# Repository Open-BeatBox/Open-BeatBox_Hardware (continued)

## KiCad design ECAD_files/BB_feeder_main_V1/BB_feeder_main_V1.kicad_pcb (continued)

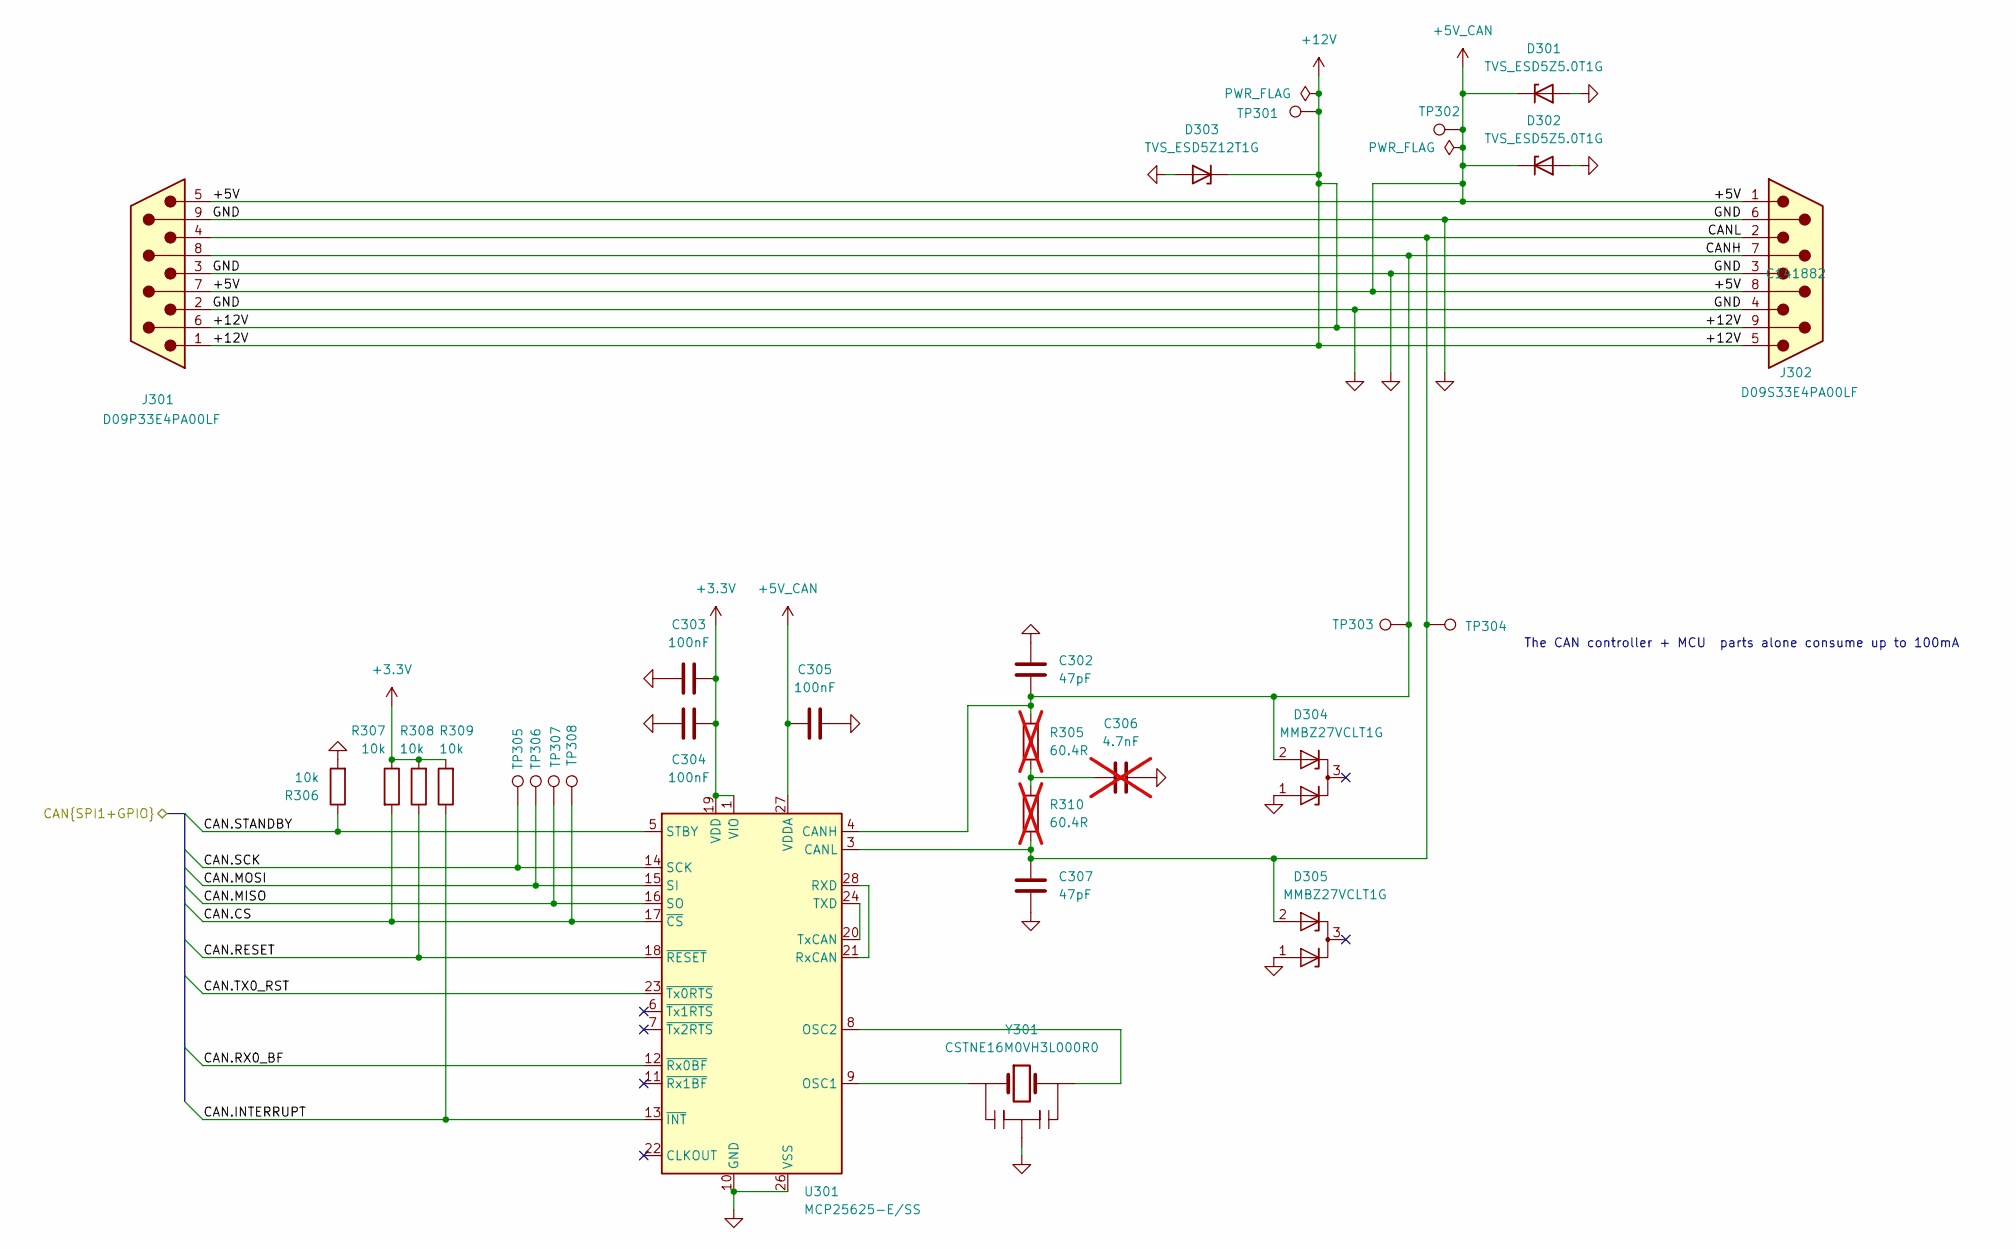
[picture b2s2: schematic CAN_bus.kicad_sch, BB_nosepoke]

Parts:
C302, C307: 47pF; C_0603_1608Metric
C303, C304, C305: 100nF; C_0603_1608Metric
C306: 4.7nF; C_0603_1608Metric; not fitted
D301, D302: TVS_ESD5Z5.0T1G; D_SOD-523; MPN ESD5Z5.0T1G; JLC Part C343989
D303: TVS_ESD5Z12T1G; D_SOD-523; MPN ESD5Z12T1G
D304, D305: MMBZ27VCLT1G; SOT-23; MPN MMBZ27VCLT1G; JLC Part C128609
J301: Conn-DB9_D09P33E4PA00LF; Conn_DB9_D09P33E4PA00LF; MPN D09P33E4PA00LF; JLC Part C19077344
J302: Conn-DB9_D09S33E4PA00LF; Conn_DB9_D09S33E4PA00LF; MPN D09S33E4PA00LF; JLC Part C141882
R305, R310: 60.4R; R_0603_1608Metric; not fitted
R306, R307, R308, R309: 10k; R_0603_1608Metric
TP301, TP302: TestPoint; TestPoint_THTPad_D2.0mm_Drill1.0mm
TP303, TP304, TP305, TP306, TP307, TP308: TestPoint; TestPoint_Pad_D1.0mm
U301: MCP25625-E/SS; SSOP-28_5.3x10.2mm_P0.65mm; MPN MCP25625-E/SS; JLC Part C184944
Y301: CSTNE16M0VH3L000R0; Resonator_SMD_Murata_CSTxExxV-3Pin_3.0x1.1mm; MPN CSTNE16M0VH3L000R0; JLC Part C1870467

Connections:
+3.3V: C303.2, C304.2, R307.1, R308.2, R309.2, U301.1 (VIO), U301.19 (VDD); also elsewhere on the board
+5V_CAN: C305.1, D301.1 (K), D302.1 (K), J301.5, J301.7, J302.1, J302.8, TP302.1 (1_1), U301.27 (VDDA); also elsewhere on the board
+12V: D303.1 (K), J301.1, J301.6, J302.5, J302.9, TP301.1 (1_1); also elsewhere on the board
/CAN bus/CAN.CS: R307.2, TP308.1 (1_1), U301.17 (~CS); also elsewhere on the board
/CAN bus/CAN.INTERRUPT: R309.1, U301.13 (~INT); also elsewhere on the board
/CAN bus/CAN.MISO: TP307.1 (1_1), U301.16 (SO); also elsewhere on the board
/CAN bus/CAN.MOSI: TP306.1 (1_1), U301.15 (SI); also elsewhere on the board
/CAN bus/CAN.RESET: R308.1, U301.18 (~RESET); also elsewhere on the board
/CAN bus/CAN.RX0_BF: U301.12 (~Rx0BF); also elsewhere on the board
/CAN bus/CAN.SCK: TP305.1 (1_1), U301.14 (SCK); also elsewhere on the board
/CAN bus/CAN.STANDBY: R306.1, U301.5 (STBY); also elsewhere on the board
/CAN bus/CAN.TX0_RST: U301.23 (~Tx0RTS); also elsewhere on the board
/CAN bus/CANH: C302.2, D304.2 (K), J301.8, J302.7, R305.2, TP303.1 (1_1), U301.4 (CANH)
/CAN bus/CANL: C307.1, D305.2 (K), J301.4, J302.2, R310.1, TP304.1 (1_1), U301.3 (CANL)
GND: C302.1, C303.1, C304.1, C305.2, C306.2, C307.2, D301.2 (A), D302.2 (A), D303.2 (A), D304.1 (K), D305.1 (K), J301.2, J301.3, J301.9, J302.3, J302.4, J302.6, R306.2, U301.10 (GND), U301.26 (VSS), Y301.2 (GND); also elsewhere on the board
unnamed: C306.1, R305.1, R310.2
unnamed: U301.9 (OSC1), Y301.1 (Input)
unnamed: U301.8 (OSC2), Y301.3 (Output)
unnamed: U301.21 (RxCAN), U301.28 (RXD)
unnamed: U301.20 (TxCAN), U301.24 (TXD)

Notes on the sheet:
The CAN controller + MCU parts alone consume up to 100mA

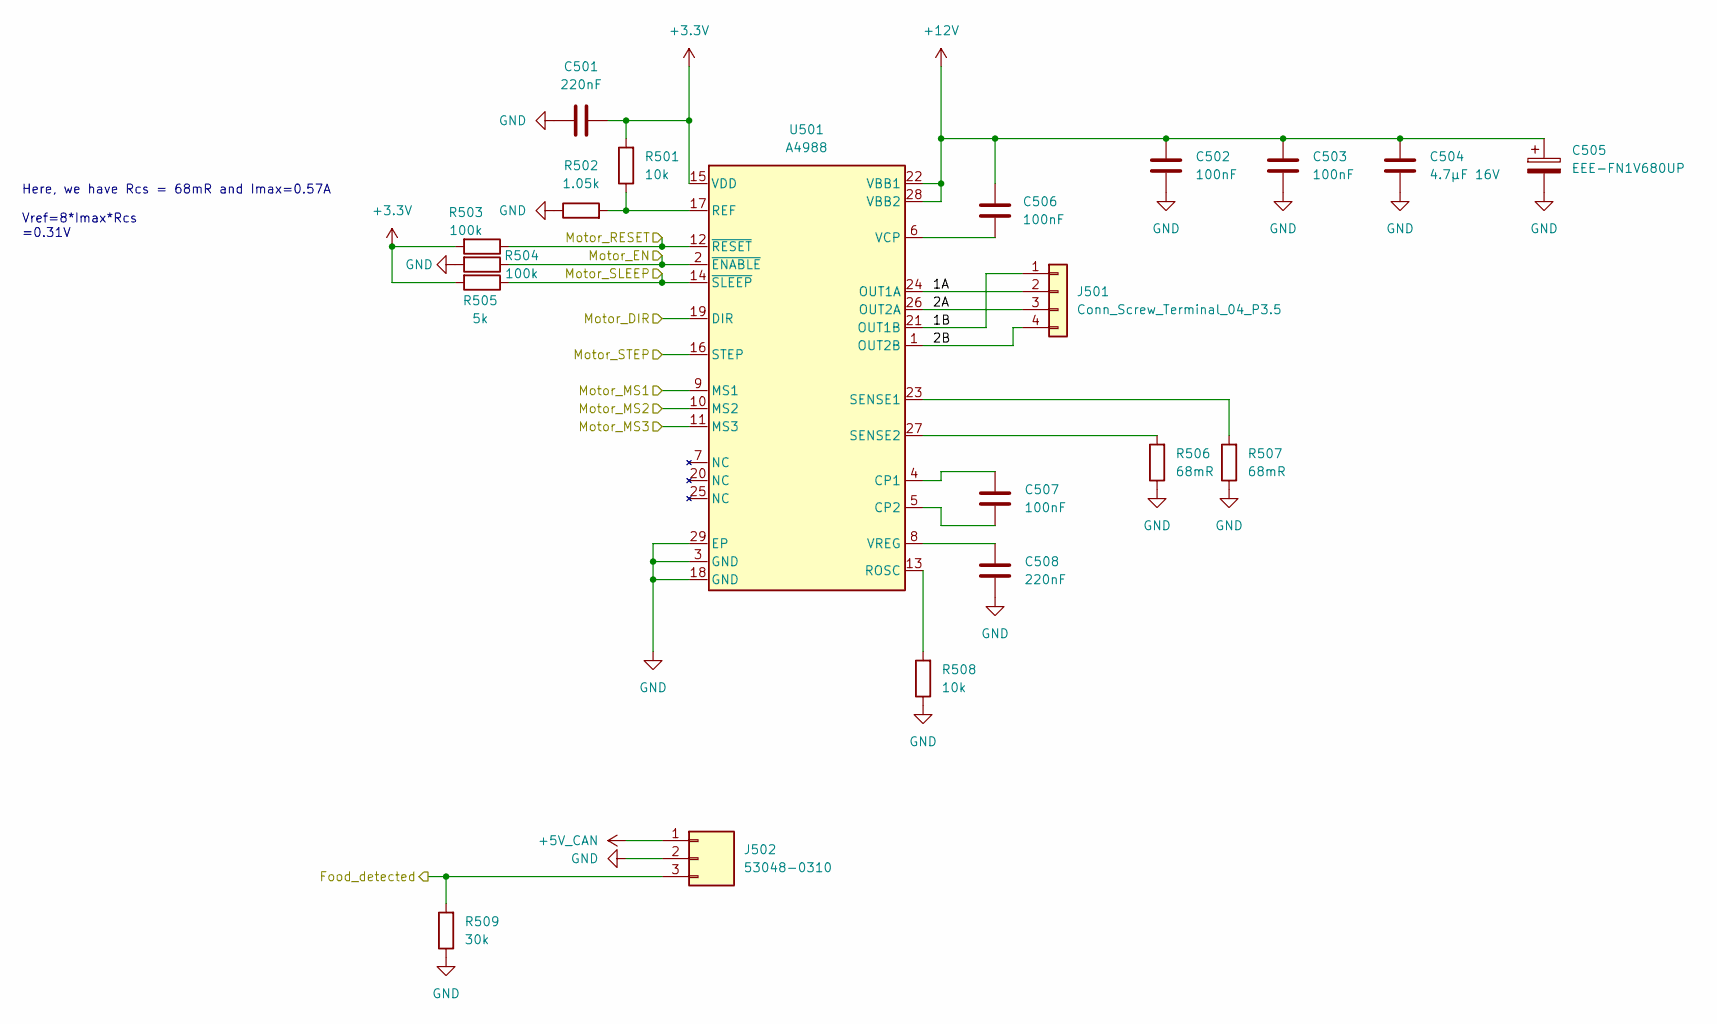
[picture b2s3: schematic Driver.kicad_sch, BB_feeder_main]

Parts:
C501, C508: 220nF; C_0603_1608Metric
C502, C503, C506, C507: 100nF; C_0603_1608Metric
C504: 4.7µF 16V; C_1206_3216Metric
C505: EEE-FN1V680UP; MPN EEE-FN1V680UP
J501: Conn_Screw_Terminal_04_P3.5; TerminalBlock_Phoenix_PT-1,5-4-3.5-H_1x04_P3.50mm_Horizontal; MPN 20020327-C041B01LF; JLC Part C2757925
J502: Conn_Picoblade_Molex_53048-0310; Conn_Molex_PicoBlade_53048-0310_1x03_P1.25mm_Horizontal; MPN 53048-0310; JLC Part C505275
R501, R508: 10k; R_0603_1608Metric
R502: 1.05k; R_0603_1608Metric
R503, R504: 100k; R_0603_1608Metric
R505: 5k; R_0603_1608Metric
R506, R507: 68mR; R_0603_1608Metric
R509: 30k; R_0603_1608Metric
U501: A4988; QFN-28-1EP_5x5mm_P0.5mm_EP3.1x3.1mm; MPN A4988SETTR-T

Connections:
+3.3V: C501.1, R501.2, R503.2, R505.2, U501.15 (VDD); also elsewhere on the board
+5V_CAN: J502.1; also elsewhere on the board
+12V: C502.1, C503.1, C504.1, C505.2, C506.2, U501.22 (VBB1), U501.28 (VBB2); also elsewhere on the board
/MCU/Food_detected: J502.3, R509.2; also elsewhere on the board
/MCU/Motor_DIR: U501.19 (DIR); also elsewhere on the board
/MCU/Motor_EN: R504.1, U501.2 (~ENABLE); also elsewhere on the board
/MCU/Motor_MS1: U501.9 (MS1); also elsewhere on the board
/MCU/Motor_MS2: U501.10 (MS2); also elsewhere on the board
/MCU/Motor_MS3: U501.11 (MS3); also elsewhere on the board
/MCU/Motor_RESET: R503.1, U501.12 (~RESET); also elsewhere on the board
/MCU/Motor_SLEEP: R505.1, U501.14 (~SLEEP); also elsewhere on the board
/MCU/Motor_STEP: U501.16 (STEP); also elsewhere on the board
/Motor driver/1A: J501.2, U501.24 (OUT1A)
/Motor driver/1B: J501.1, U501.21 (OUT1B)
/Motor driver/2A: J501.3, U501.26 (OUT2A)
/Motor driver/2B: J501.4, U501.1 (OUT2B)
GND: C501.2, C502.2, C503.2, C504.2, C505.1, C508.2, J502.2, R502.1, R504.2, R506.1, R507.1, R508.1, R509.1, U501.3 (GND), U501.18 (GND), U501.29 (EP); also elsewhere on the board
unnamed: C507.1, U501.4 (CP1)
unnamed: C507.2, U501.5 (CP2)
unnamed: R501.1, R502.2, U501.17 (REF)
unnamed: R508.2, U501.13 (ROSC)
unnamed: R507.2, U501.23 (SENSE1)
unnamed: R506.2, U501.27 (SENSE2)
unnamed: C506.1, U501.6 (VCP)
unnamed: C508.1, U501.8 (VREG)

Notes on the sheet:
Here, we have Rcs = 68mR and Imax=0.57A Vref=8*Imax*Rcs =0.31V

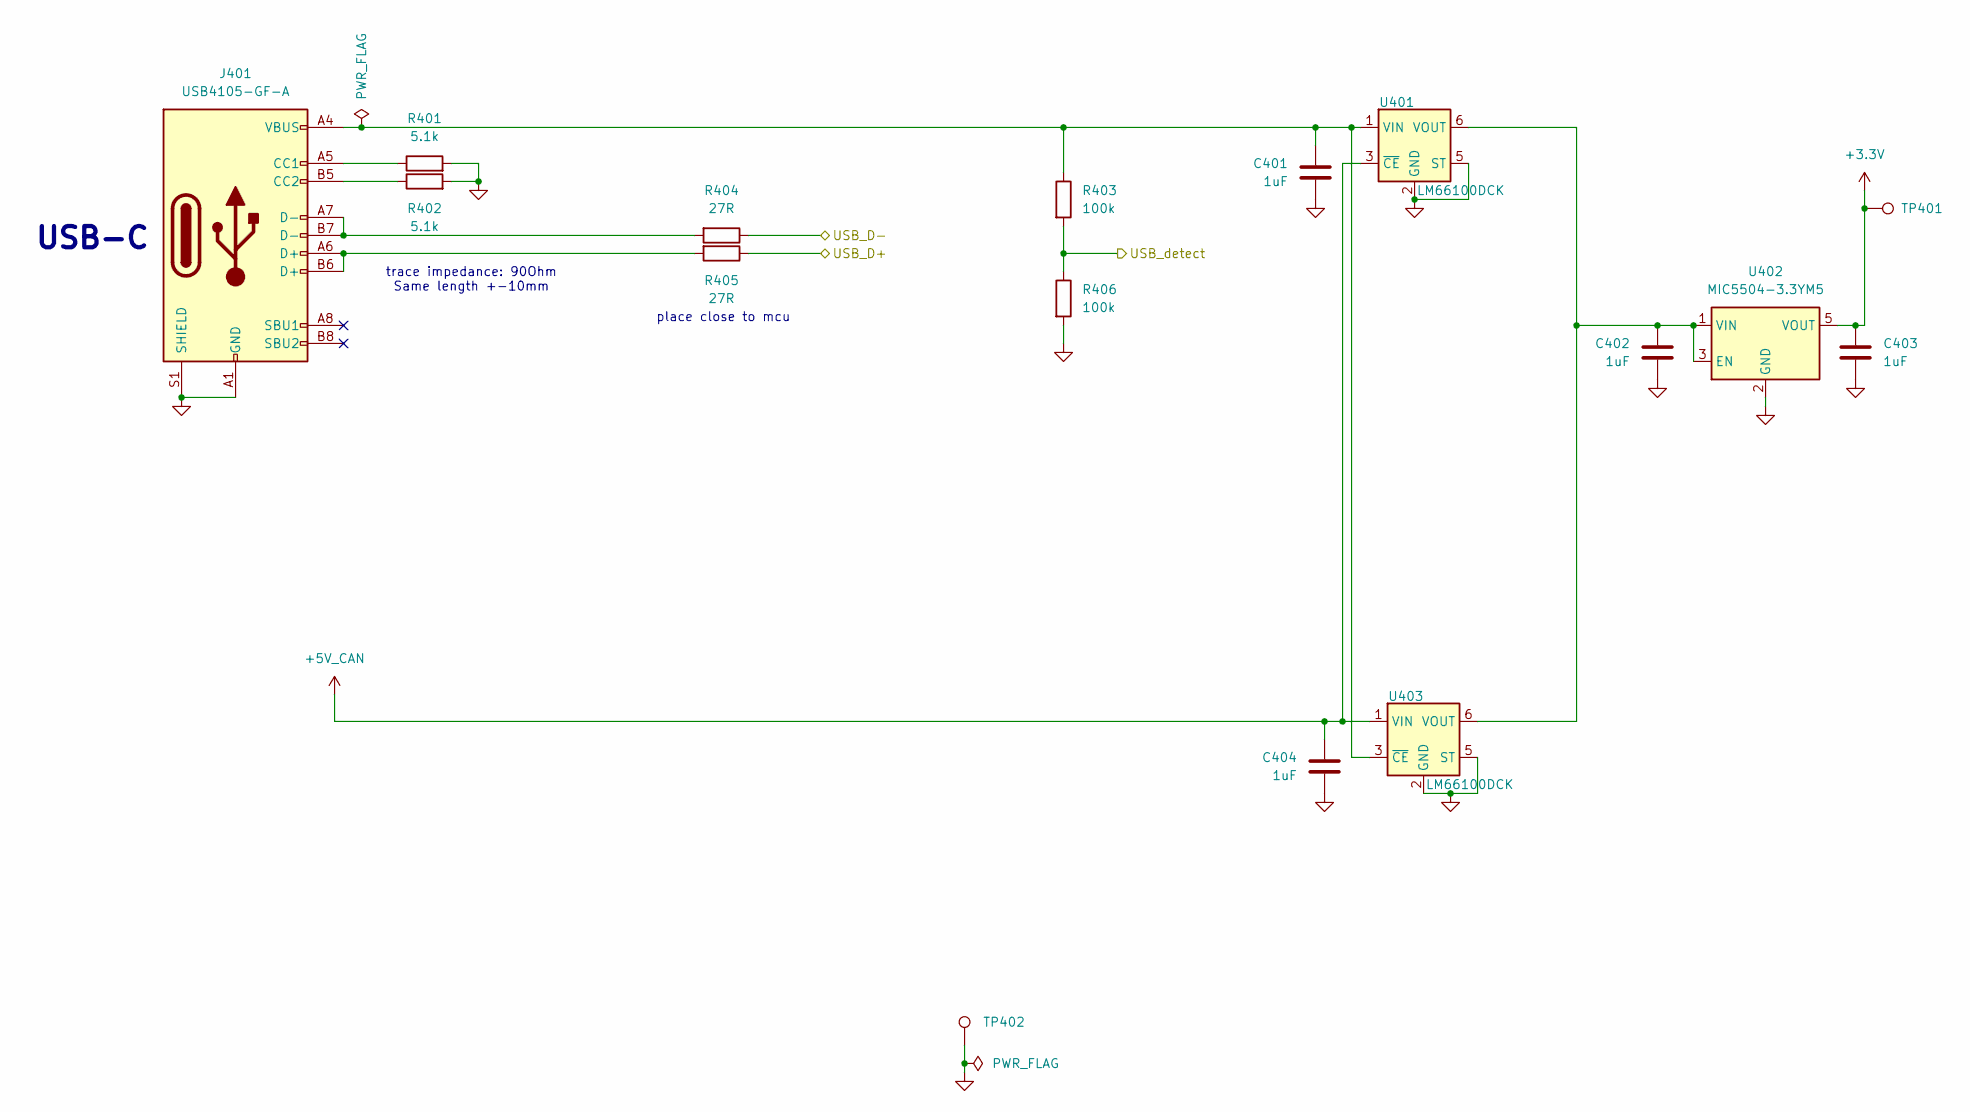
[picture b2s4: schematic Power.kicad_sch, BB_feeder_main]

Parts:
C401, C402, C403, C404: 1uF; C_0603_1608Metric
J401: Conn_USB-C_USB4105-GF-A; Conn_USB_C_Receptacle_GCT_USB4105-xx-A_16P_TopMnt_Horizontal; MPN USB4105-GF-A; JLC Part C393939
R401, R402: 5.1k; R_0603_1608Metric
R403, R406: 100k; R_0603_1608Metric
R404, R405: 27R; R_0603_1608Metric
TP401, TP402: TestPoint; TestPoint_THTPad_D2.0mm_Drill1.0mm
U401, U403: LM66100DCK; SOT-363_SC-70-6; MPN LM66100DCKR; JLC Part C2869734
U402: MIC5504-3.3YM5; SOT-23-5; MPN MIC5504-3.3YM5; JLC Part C88419

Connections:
+3.3V: C403.1, TP401.1 (1_1), U402.5 (VOUT); also elsewhere on the board
+5V_CAN: C404.2, U401.3 (~CE), U403.1 (VIN); also elsewhere on the board
/MCU/USB_D+: R405.1; also elsewhere on the board
/MCU/USB_D-: R404.1; also elsewhere on the board
/MCU/USB_detect: R403.2, R406.1; also elsewhere on the board
GND: C401.1, C402.2, C403.2, C404.1, J401.A1 (GND), J401.A12 (GND), J401.B1 (GND), J401.B12 (GND), J401.S1 (SHIELD), R401.2, R402.2, R406.2, TP402.1 (1_1), U401.2 (GND), U401.5 (ST), U402.2 (GND), U403.2 (GND), U403.5 (ST); also elsewhere on the board
unnamed: J401.A5 (CC1), R401.1
unnamed: J401.B5 (CC2), R402.1
unnamed: J401.A6 (D+), J401.B6 (D+), R405.2
unnamed: J401.A7 (D-), J401.B7 (D-), R404.2
unnamed: C401.2, J401.A4 (VBUS), J401.A9 (VBUS), J401.B4 (VBUS), J401.B9 (VBUS), R403.1, U401.1 (VIN), U403.3 (~CE)
unnamed: C402.1, U401.6 (VOUT), U402.1 (VIN), U402.3 (EN), U403.6 (VOUT)

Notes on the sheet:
place close to mcu
trace impedance: 90Ohm Same length +-10mm
USB-C

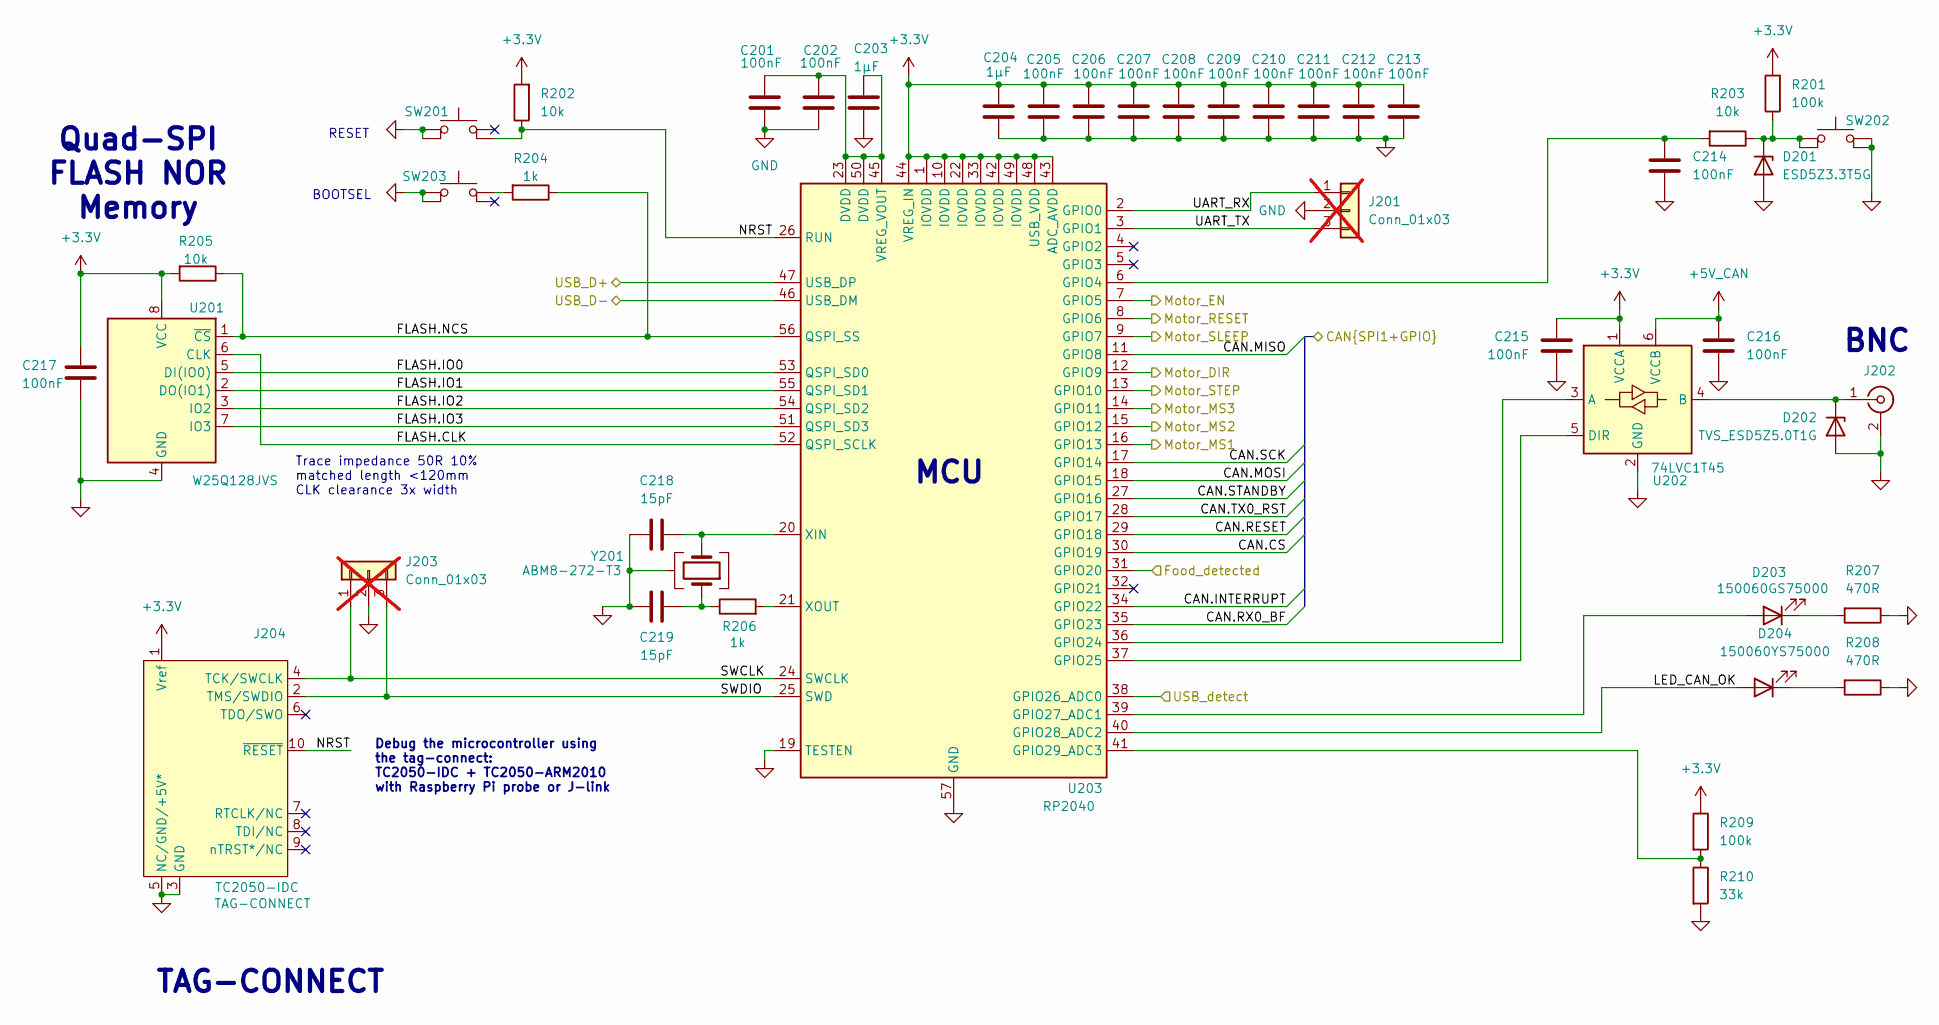
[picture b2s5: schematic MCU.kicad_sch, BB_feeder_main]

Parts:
C201, C202, C205, C206, C207, C208, C209, C210, C211, C212, C213, C214, C215, C216, C217: 100nF; C_0603_1608Metric
C203, C204: 1µF; C_0603_1608Metric
C218, C219: 15pF; C_0603_1608Metric
D201: TVS_ESD5Z3.3T5G; D_SOD-523; MPN ESD5Z3.3T5G; JLC Part C22440024
D202: TVS_ESD5Z5.0T1G; D_SOD-523; MPN ESD5Z5.0T1G; JLC Part C343989
D203: LED_150060GS75000; LED_0603_1608Metric; MPN 150060GS75000; JLC Part C5252984
D204: LED_150060YS75000; LED_0603_1608Metric; MPN 150060YS75000; JLC Part C6784997
J201, J203: Conn_01x03; PinHeader_1x03_P2.54mm_Vertical; not fitted
J202: Conn_BNC_KH-BNC50-3511; KH-BNC50-3511; MPN KH-BNC50-3511; JLC Part C2837587
J204: Conn_TagConnect_TC2050-IDC; Tag-Connect_TC2050-IDC-FP_2x05_P1.27mm_Vertical; MPN TC2050-IDC
R201, R209: 100k; R_0603_1608Metric
R202, R203, R205: 10k; R_0603_1608Metric
R204, R206: 1k; R_0603_1608Metric
R207, R208: 470R; R_0603_1608Metric
R210: 33k; R_0603_1608Metric
SW201, SW202, SW203: SW_TL3305AF160QG; SW_Push_TL3305; MPN TL3305AF160QG; JLC Part C18078070
U201: W25Q128JVS; SOIC-8_W25Q128JV; MPN W25Q128JVS; JLC Part C97521
U202: 74LVC1T45; SOT-363_SC-70-6; MPN 74LVC1T45DW-7; JLC Part C168855
U203: RP2040; QFN-56-1EP_7x7mm_P0.4mm_EP3.2x3.2mm; MPN RP2040; JLC Part C2040
Y201: Crystal_ABM8-272-T3; Crystal_SMD_Abracon_ABM8; MPN ABM8-272-T3; JLC Part C20625731

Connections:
+3.3V: C204.1, C205.1, C206.1, C207.1, C208.1, C209.1, C210.1, C211.1, C212.1, C213.1, C215.2, C217.2, J204.1 (Vref), R201.2, R202.2, R205.2, R209.1, U201.8 (VCC), U202.1 (VCCA), U203.1 (IOVDD), U203.10 (IOVDD), U203.22 (IOVDD), U203.33 (IOVDD), U203.42 (IOVDD), U203.43 (ADC_AVDD), U203.44 (VREG_IN), U203.48 (USB_VDD), U203.49 (IOVDD); also elsewhere on the board
+5V_CAN: C216.2, U202.6 (VCCB); also elsewhere on the board
/CAN bus/CAN.CS: U203.30 (GPIO19); also elsewhere on the board
/CAN bus/CAN.INTERRUPT: U203.34 (GPIO22); also elsewhere on the board
/CAN bus/CAN.MISO: U203.11 (GPIO8); also elsewhere on the board
/CAN bus/CAN.MOSI: U203.18 (GPIO15); also elsewhere on the board
/CAN bus/CAN.RESET: U203.29 (GPIO18); also elsewhere on the board
/CAN bus/CAN.RX0_BF: U203.35 (GPIO23); also elsewhere on the board
/CAN bus/CAN.SCK: U203.17 (GPIO14); also elsewhere on the board
/CAN bus/CAN.STANDBY: U203.27 (GPIO16); also elsewhere on the board
/CAN bus/CAN.TX0_RST: U203.28 (GPIO17); also elsewhere on the board
/MCU/FLASH.CLK: U201.6 (CLK), U203.52 (QSPI_SCLK)
/MCU/FLASH.IO0: U201.5 (DI(IO0)), U203.53 (QSPI_SD0)
/MCU/FLASH.IO1: U201.2 (DO(IO1)), U203.55 (QSPI_SD1)
/MCU/FLASH.IO2: U201.3 (IO2), U203.54 (QSPI_SD2)
/MCU/FLASH.IO3: U201.7 (IO3), U203.51 (QSPI_SD3)
/MCU/FLASH.NCS: R204.1, R205.1, U201.1 (~CS), U203.56 (QSPI_SS)
/MCU/Food_detected: U203.31 (GPIO20); also elsewhere on the board
/MCU/LED_CAN_OK: D204.2 (A), U203.40 (GPIO28_ADC2)
/MCU/Motor_DIR: U203.12 (GPIO9); also elsewhere on the board
/MCU/Motor_EN: U203.7 (GPIO5); also elsewhere on the board
/MCU/Motor_MS1: U203.16 (GPIO13); also elsewhere on the board
/MCU/Motor_MS2: U203.15 (GPIO12); also elsewhere on the board
/MCU/Motor_MS3: U203.14 (GPIO11); also elsewhere on the board
/MCU/Motor_RESET: U203.8 (GPIO6); also elsewhere on the board
/MCU/Motor_SLEEP: U203.9 (GPIO7); also elsewhere on the board
/MCU/Motor_STEP: U203.13 (GPIO10); also elsewhere on the board
/MCU/NRST: J204.10 (~RESET), R202.1, SW201.2, U203.26 (RUN)
/MCU/SWCLK: J203.1, J204.4 (TCK/SWCLK), U203.24 (SWCLK)
/MCU/SWDIO: J203.3, J204.2 (TMS/SWDIO), U203.25 (SWD)
/MCU/UART_RX: J201.1, U203.2 (GPIO0)
/MCU/UART_TX: J201.3, U203.3 (GPIO1)
/MCU/USB_D+: U203.47 (USB_DP); also elsewhere on the board
/MCU/USB_D-: U203.46 (USB_DM); also elsewhere on the board
/MCU/USB_detect: U203.38 (GPIO26_ADC0); also elsewhere on the board
GND: C201.1, C202.2, C203.1, C204.2, C205.2, C206.2, C207.2, C208.2, C209.2, C210.2, C211.2, C212.2, C213.2, C214.2, C215.1, C216.1, C217.1, C218.1, C219.1, D201.2 (A), D202.2 (A), J201.2, J202.2 (Ext), J203.2, J204.3 (GND), J204.5 (NC/GND/+5V*), R207.1, R208.1, R210.2, SW201.3, SW201.4, SW202.3, SW202.4, SW203.1, SW203.2, U201.4 (GND), U202.2 (GND), U203.19 (TESTEN), U203.57 (GND), Y201.2, Y201.4; also elsewhere on the board
unnamed: C219.2, R206.1, Y201.1
unnamed: D201.1 (K), R201.1, R203.1, SW202.1, SW202.2
unnamed: D202.1 (K), J202.1 (In), U202.4 (B)
unnamed: D203.2 (A), U203.39 (GPIO27_ADC1)
unnamed: D203.1 (K), R207.2
unnamed: D204.1 (K), R208.2
unnamed: R204.2, SW203.3
unnamed: U202.3 (A), U203.36 (GPIO24)
unnamed: U202.5 (DIR), U203.37 (GPIO25)
unnamed: C214.1, R203.2, U203.6 (GPIO4)
unnamed: R209.2, R210.1, U203.41 (GPIO29_ADC3)
unnamed: C201.2, C202.1, C203.2, U203.23 (DVDD), U203.45 (VREG_VOUT), U203.50 (DVDD)
unnamed: C218.2, U203.20 (XIN), Y201.3
unnamed: R206.2, U203.21 (XOUT)

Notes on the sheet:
Trace impedance 50R 10% matched length <120mm CLK clearance 3x width
RESET
Quad-SPI FLASH NOR Memory
Debug the microcontroller using the tag-connect: TC2050-IDC + TC2050-ARM2010 with Raspberry Pi probe or J-link
TAG-CONNECT
MCU
BNC
BOOTSEL

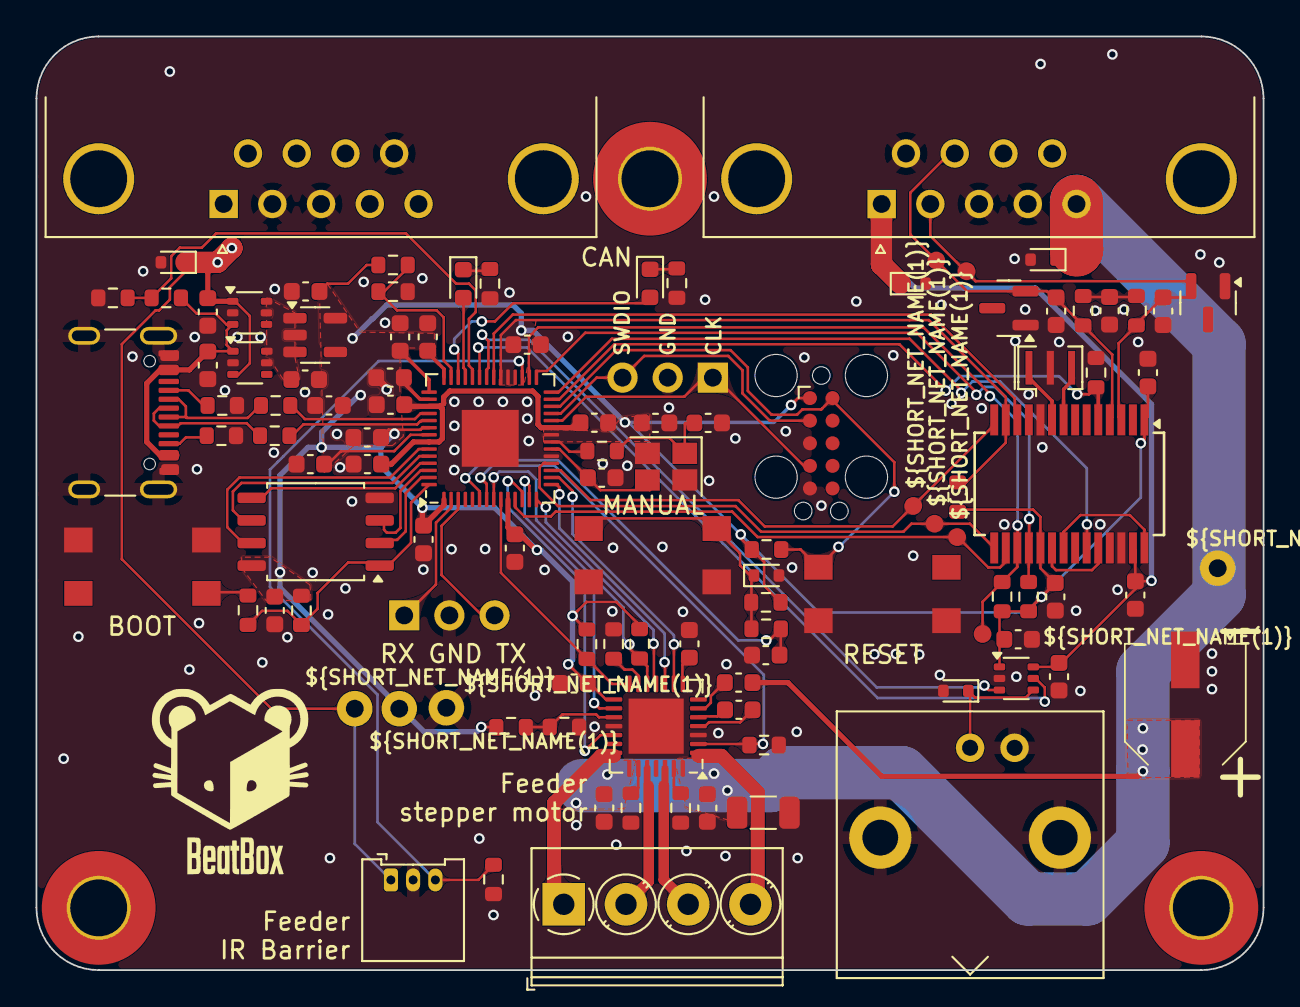
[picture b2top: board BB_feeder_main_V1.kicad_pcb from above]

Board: 4 copper layers, 69.0 x 52.5 mm, 112 parts (0 on the bottom side), 76 nets.

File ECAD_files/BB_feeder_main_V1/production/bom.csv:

Designator,Footprint,Quantity,Value,LCSC Part #
"C201, C202, C205, C206, C207, C208, C209, C210, C211, C212, C213, C214, C215, C216, C217, C303, C304, C305, C502, C503, C506, C507",0603,22,100nF,
"C203, C204",0603,2,1µF,
"C218, C219",0603,2,15pF,
"C302, C307",0603,2,47pF,
"C401, C402, C403, C404",0603,4,1uF,
"C501, C508",0603,2,220nF,
C504,1206,1,4.7µF 16V,
C505,EEE-FN1V680UP,1,EEE-FN1V680UP,EEE-FN1V680UP
D201,D_SOD-523,1,TVS_ESD5Z3.3T5G,ESD5Z3.3T5G
"D202, D301, D302",D_SOD-523,3,TVS_ESD5Z5.0T1G,ESD5Z5.0T1G
D203,0603,1,LED_150060GS75000,150060GS75000
D204,0603,1,LED_150060YS75000,150060YS75000
D303,D_SOD-523,1,TVS_ESD5Z12T1G,ESD5Z12T1G
"D304, D305",SOT-23,2,MMBZ27VCLT1G,MMBZ27VCLT1G
J202,KH-BNC50-3511,1,Conn_BNC_KH-BNC50-3511,KH-BNC50-3511
J301,Conn_DB9_D09P33E4PA00LF,1,Conn-DB9_D09P33E4PA00LF,D09P33E4PA00LF
J302,Conn_DB9_D09S33E4PA00LF,1,Conn-DB9_D09S33E4PA00LF,D09S33E4PA00LF
J401,Conn_USB_C_Receptacle_GCT_USB4105-xx-A_16P_TopMnt_Horizontal,1,Conn_USB-C_USB4105-GF-A,USB4105-GF-A
J501,"TerminalBlock_Phoenix_PT-1,5-4-3.5-H_1x04_P3.50mm_Horizontal",1,Conn_Screw_Terminal_04_P3.5,20020327-C041B01LF
J502,Conn_Molex_PicoBlade_53048-0310_1x03_P1.25mm_Horizontal,1,Conn_Picoblade_Molex_53048-0310,53048-0310
"R201, R209, R403, R406, R503, R504",0603,6,100k,
"R202, R203, R205, R306, R307, R308, R309, R501, R508",0603,9,10k,
"R204, R206",0603,2,1k,
"R207, R208",0603,2,470R,
R210,0603,1,33k,
"R401, R402",0603,2,5.1k,
"R404, R405",0603,2,27R,
R502,0603,1,1.05k,
R505,0603,1,5k,
"R506, R507",0603,2,68mR,
R509,0603,1,30k,
"SW201, SW202, SW203",SW_Push_TL3305,3,SW_TL3305AF160QG,TL3305AF160QG
U201,SOIC-8_W25Q128JV,1,W25Q128JVS,
U202,SOT-363_SC-70-6,1,74LVC1T45,74LVC1T45DW-7
U203,QFN-56-1EP_7x7mm_P0.4mm_EP3.2x3.2mm,1,RP2040,RP2040
U301,SSOP-28_5.3x10.2mm_P0.65mm,1,MCP25625-E/SS,MCP25625-E/SS
"U401, U403",SOT-363_SC-70-6,2,LM66100DCK,LM66100DCKR
U402,SOT-23-5,1,MIC5504-3.3YM5,MIC5504-3.3YM5
U501,QFN-28-1EP_5x5mm_P0.5mm_EP3.1x3.1mm,1,A4988,A4988SETTR-T
Y201,Crystal_SMD_Abracon_ABM8,1,Crystal_ABM8-272-T3,ABM8-272-T3
Y301,Resonator_SMD_Murata_CSTxExxV-3Pin_3.0x1.1mm,1,CSTNE16M0VH3L000R0,CSTNE16M0VH3L000R0

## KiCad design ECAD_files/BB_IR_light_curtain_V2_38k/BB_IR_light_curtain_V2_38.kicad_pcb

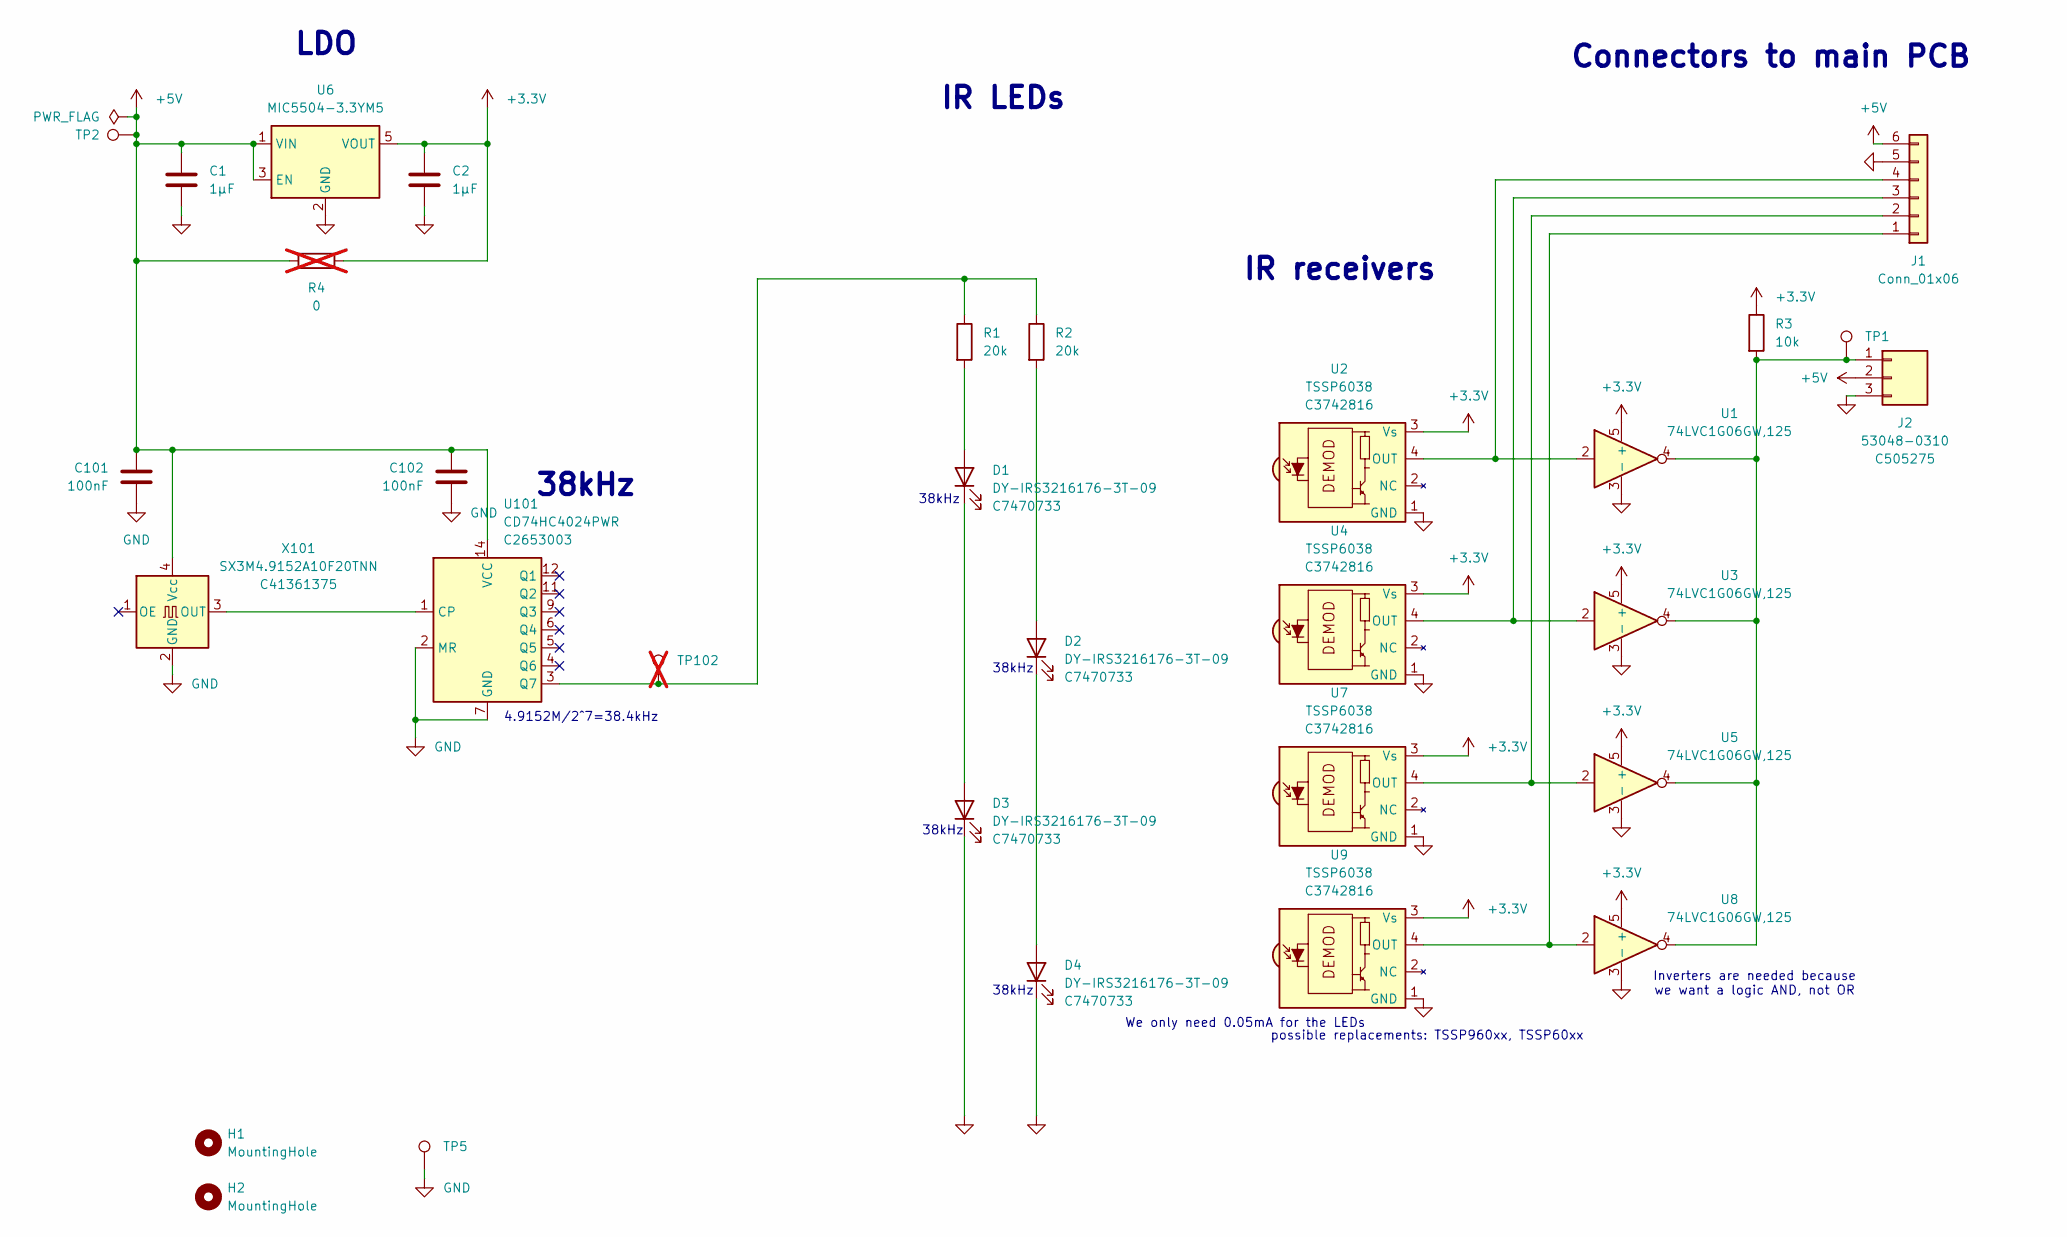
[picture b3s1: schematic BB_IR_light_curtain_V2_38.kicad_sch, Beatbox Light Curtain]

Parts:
C1, C2: 1µF; C_0603_1608Metric
C101, C102: 100nF; C_0603_1608Metric
D1, D2, D3, D4: DY-IRS3216176-3T-09; LED_1206_3216Metric; MPN DY-IRS3216176-3T-09; JLCPCB Part C7470733
H1, H2: MountingHole; MountingHole_3.2mm_M3_Pad_TopBottom
J1: Conn_01x06; Conn_Molex_PicoBlade_53048-0610_1x06_P1.25mm_Horizontal
J2: Conn_Picoblade_Molex_53048-0310; Conn_Molex_PicoBlade_53048-0310_1x03_P1.25mm_Horizontal; MPN 53048-0310; JLCPCB Part C505275
R1, R2: 20k; R_0603_1608Metric_Pad0.98x0.95mm_HandSolder
R3: 10k; R_0603_1608Metric
R4: 0; R_0603_1608Metric; not fitted
TP1, TP2, TP5: TestPoint; TestPoint_Pad_D1.0mm
TP102: TestPoint; TestPoint_Pad_D1.0mm; not fitted
U1, U3, U5, U8: 74LVC1G06GW,125; SOT-353_SC-70-5; MPN 74LVC1G06GW,125; JLCPCB Part C426704
U2, U4, U7, U9: TSSP6038; Vishay-panhead; MPN TSSP6038; JLCPCB Part C3742816
U6: MIC5504-3.3YM5; SOT-23-5; MPN MIC5504-3.3YM5; JLCPCB Part C88419
U101: CD74HC4024PWR; TSSOP-14_4.4x5mm_P0.65mm; MPN CD74HC4024PWR; JLCPCB Part C2653003
X101: SX3M4.9152A10F20TNN; Crystal_SMD_3225-4Pin_3.2x2.5mm; MPN SX3M4.9152A10F20TNN; JLCPCB Part C41361375

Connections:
+3.3V: C2.1, R3.1, R4.2, U1.5 (+), U2.3 (Vs), U3.5 (+), U4.3 (Vs), U5.5 (+), U6.5 (VOUT), U7.3 (Vs), U8.5 (+), U9.3 (Vs)
+5V: C1.1, C101.2, C102.2, J1.6, J2.2, R4.1, TP2.1 (1_1), U6.1 (VIN), U6.3 (EN), U101.14 (VCC), X101.4 (Vcc)
GND: C1.2, C2.2, C101.1, C102.1, D3.1 (K), D4.1 (K), J1.5, J2.3, TP5.1 (1_1), U1.3 (-), U2.1 (GND), U3.3 (-), U4.1 (GND), U5.3 (-), U6.2 (GND), U7.1 (GND), U8.3 (-), U9.1 (GND), U101.2 (MR), U101.7 (GND), X101.2 (GND)
unnamed: D1.2 (A), R1.2
unnamed: D1.1 (K), D3.2 (A)
unnamed: D2.2 (A), R2.2
unnamed: D2.1 (K), D4.2 (A)
unnamed: J1.1, U8.2, U9.4 (OUT)
unnamed: J1.2, U5.2, U7.4 (OUT)
unnamed: J1.3, U3.2, U4.4 (OUT)
unnamed: J1.4, U1.2, U2.4 (OUT)
unnamed: J2.1, R3.2, TP1.1 (1_1), U1.4, U3.4, U5.4, U8.4
unnamed: U101.1 (CP), X101.3 (OUT)
unnamed: R1.1, R2.1, TP102.1 (1_1), U101.3 (Q7)

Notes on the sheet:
LDO
38kHz
4.9152M/2^7=38.4kHz
We only need 0.05mA for the LEDs
IR LEDs
Inverters are needed because we want a logic AND, not OR
IR receivers
Connectors to main PCB
possible replacements: TSSP960xx, TSSP60xx

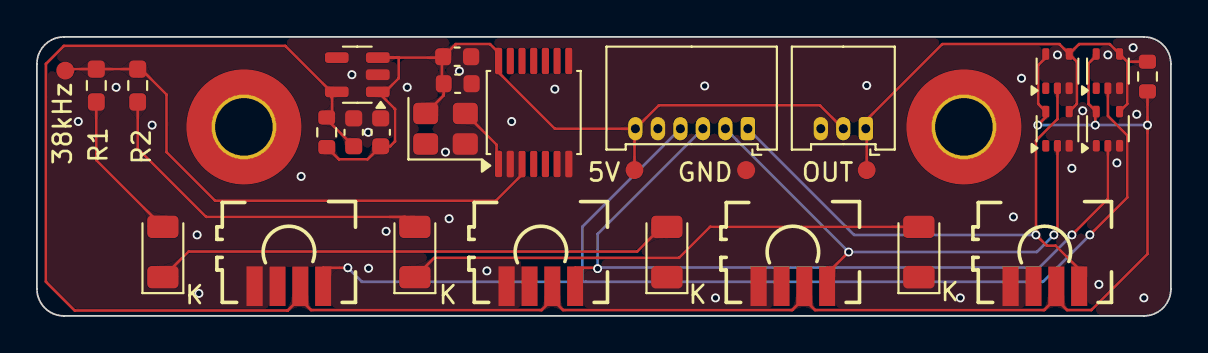
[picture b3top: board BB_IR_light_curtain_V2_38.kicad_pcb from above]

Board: 4 copper layers, 63.0 x 15.5 mm, 31 parts (0 on the bottom side), 14 nets.
